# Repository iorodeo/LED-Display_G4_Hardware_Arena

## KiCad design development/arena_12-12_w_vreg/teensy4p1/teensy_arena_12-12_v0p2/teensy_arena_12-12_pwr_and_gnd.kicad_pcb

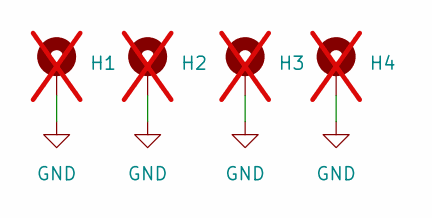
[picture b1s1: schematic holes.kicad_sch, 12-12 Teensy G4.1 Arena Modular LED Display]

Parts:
H1, H2, H3, H4: MountingHole_Pad; MountingHole_4.5mm_Pad; not fitted

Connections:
GND: H1.1, H2.1, H3.1, H4.1; also elsewhere on the board

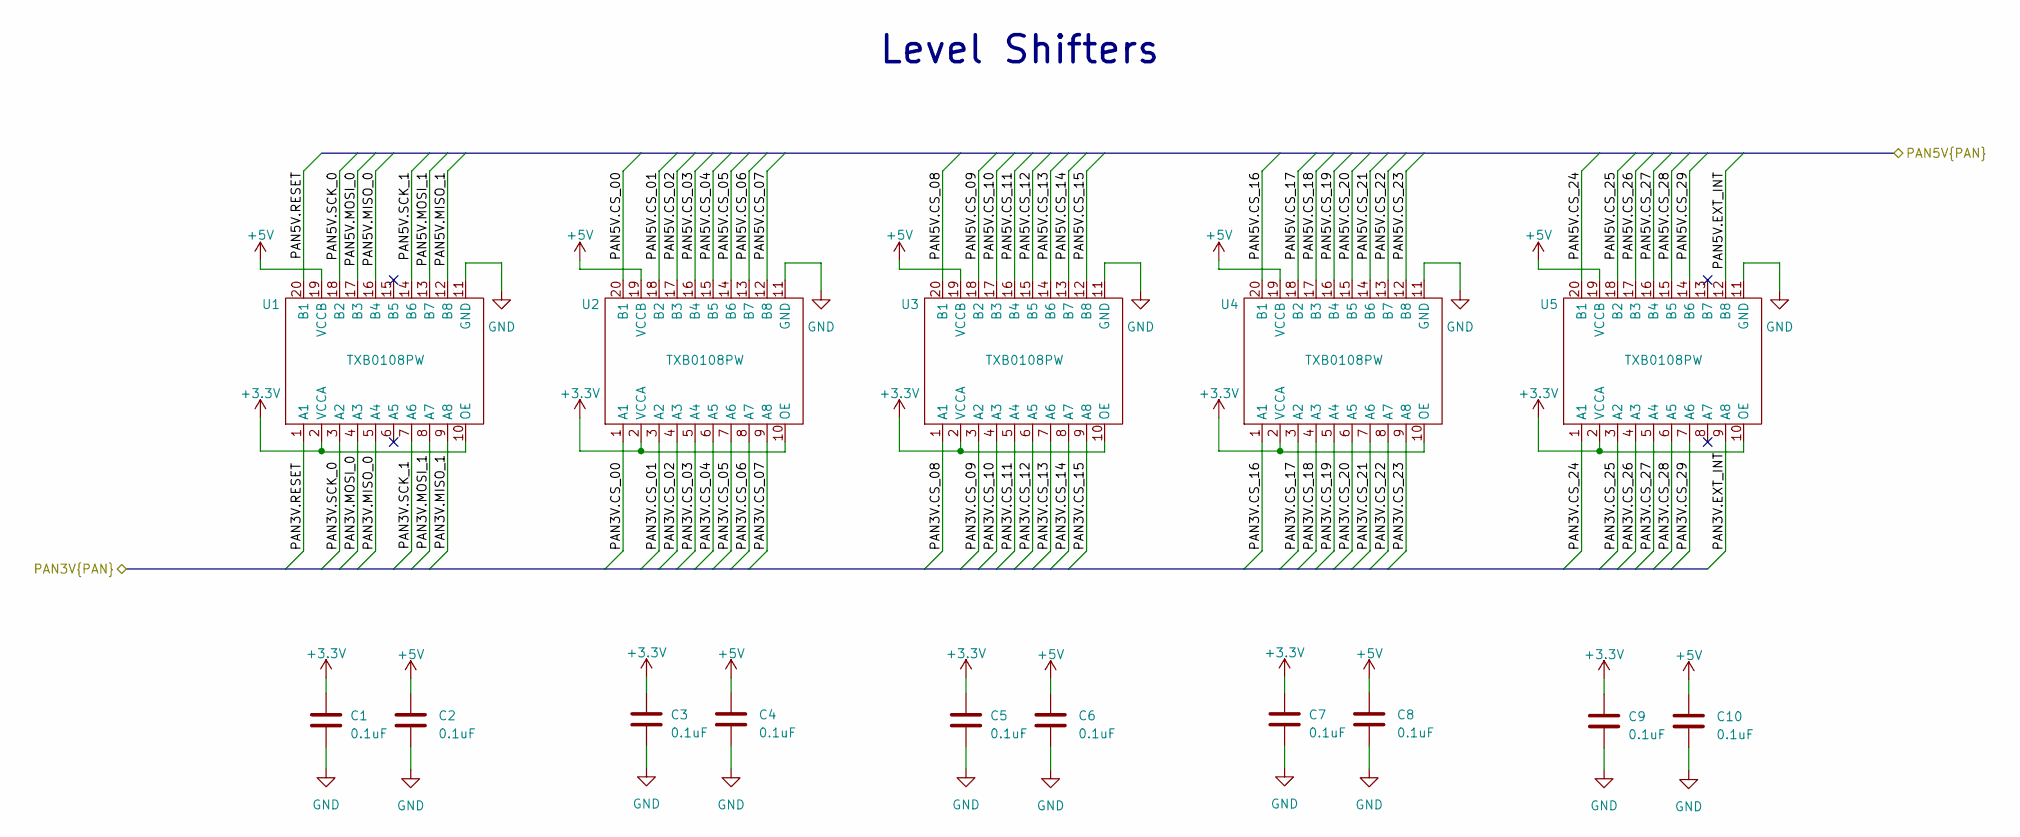
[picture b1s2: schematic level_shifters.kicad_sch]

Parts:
C1, C2, C3, C4, C5, C6, C7, C8, C9, C10: 0.1uF; C_0603_1608Metric
U1, U2, U3, U4, U5: TXB0108PW; TSSOP-20_4.4x6.5mm_P0.65mm

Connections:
+3.3V: C1.1, C3.1, C5.1, C7.1, C9.1, U1.2 (VCCA), U1.10 (OE), U2.2 (VCCA), U2.10 (OE), U3.2 (VCCA), U3.10 (OE), U4.2 (VCCA), U4.10 (OE), U5.2 (VCCA), U5.10 (OE); also elsewhere on the board
+5V: C2.1, C4.1, C6.1, C8.1, C10.1, U1.19 (VCCB), U2.19 (VCCB), U3.19 (VCCB), U4.19 (VCCB), U5.19 (VCCB); also elsewhere on the board
/Level Shifters/PAN3V.CS_00: U2.1 (A1); also elsewhere on the board
/Level Shifters/PAN3V.CS_01: U2.3 (A2); also elsewhere on the board
/Level Shifters/PAN3V.CS_02: U2.4 (A3); also elsewhere on the board
/Level Shifters/PAN3V.CS_03: U2.5 (A4); also elsewhere on the board
/Level Shifters/PAN3V.CS_04: U2.6 (A5); also elsewhere on the board
/Level Shifters/PAN3V.CS_05: U2.7 (A6); also elsewhere on the board
/Level Shifters/PAN3V.CS_06: U2.8 (A7); also elsewhere on the board
/Level Shifters/PAN3V.CS_07: U2.9 (A8); also elsewhere on the board
/Level Shifters/PAN3V.CS_08: U3.1 (A1); also elsewhere on the board
/Level Shifters/PAN3V.CS_09: U3.3 (A2); also elsewhere on the board
/Level Shifters/PAN3V.CS_10: U3.4 (A3); also elsewhere on the board
/Level Shifters/PAN3V.CS_11: U3.5 (A4); also elsewhere on the board
/Level Shifters/PAN3V.CS_12: U3.6 (A5); also elsewhere on the board
/Level Shifters/PAN3V.CS_13: U3.7 (A6); also elsewhere on the board
/Level Shifters/PAN3V.CS_14: U3.8 (A7); also elsewhere on the board
/Level Shifters/PAN3V.CS_15: U3.9 (A8); also elsewhere on the board
/Level Shifters/PAN3V.CS_16: U4.1 (A1); also elsewhere on the board
/Level Shifters/PAN3V.CS_17: U4.3 (A2); also elsewhere on the board
/Level Shifters/PAN3V.CS_18: U4.4 (A3); also elsewhere on the board
/Level Shifters/PAN3V.CS_19: U4.5 (A4); also elsewhere on the board
/Level Shifters/PAN3V.CS_20: U4.6 (A5); also elsewhere on the board
/Level Shifters/PAN3V.CS_21: U4.7 (A6); also elsewhere on the board
/Level Shifters/PAN3V.CS_22: U4.8 (A7); also elsewhere on the board
/Level Shifters/PAN3V.CS_23: U4.9 (A8); also elsewhere on the board
/Level Shifters/PAN3V.CS_24: U5.1 (A1); also elsewhere on the board
/Level Shifters/PAN3V.CS_25: U5.3 (A2); also elsewhere on the board
/Level Shifters/PAN3V.CS_26: U5.4 (A3); also elsewhere on the board
/Level Shifters/PAN3V.CS_27: U5.5 (A4); also elsewhere on the board
/Level Shifters/PAN3V.CS_28: U5.6 (A5); also elsewhere on the board
/Level Shifters/PAN3V.CS_29: U5.7 (A6); also elsewhere on the board
/Level Shifters/PAN3V.EXT_INT: U5.9 (A8); also elsewhere on the board
/Level Shifters/PAN3V.MISO_0: U1.5 (A4); also elsewhere on the board
/Level Shifters/PAN3V.MISO_1: U1.9 (A8); also elsewhere on the board
/Level Shifters/PAN3V.MOSI_0: U1.4 (A3); also elsewhere on the board
/Level Shifters/PAN3V.MOSI_1: U1.8 (A7); also elsewhere on the board
/Level Shifters/PAN3V.RESET: U1.1 (A1); also elsewhere on the board
/Level Shifters/PAN3V.SCK_0: U1.3 (A2); also elsewhere on the board
/Level Shifters/PAN3V.SCK_1: U1.7 (A6); also elsewhere on the board
/Level Shifters/PAN5V.CS_00: U2.20 (B1); also elsewhere on the board
/Level Shifters/PAN5V.CS_01: U2.18 (B2); also elsewhere on the board
/Level Shifters/PAN5V.CS_02: U2.17 (B3); also elsewhere on the board
/Level Shifters/PAN5V.CS_03: U2.16 (B4); also elsewhere on the board
/Level Shifters/PAN5V.CS_04: U2.15 (B5); also elsewhere on the board
/Level Shifters/PAN5V.CS_05: U2.14 (B6); also elsewhere on the board
/Level Shifters/PAN5V.CS_06: U2.13 (B7); also elsewhere on the board
/Level Shifters/PAN5V.CS_07: U2.12 (B8); also elsewhere on the board
/Level Shifters/PAN5V.CS_08: U3.20 (B1); also elsewhere on the board
/Level Shifters/PAN5V.CS_09: U3.18 (B2); also elsewhere on the board
/Level Shifters/PAN5V.CS_10: U3.17 (B3); also elsewhere on the board
/Level Shifters/PAN5V.CS_11: U3.16 (B4); also elsewhere on the board
/Level Shifters/PAN5V.CS_12: U3.15 (B5); also elsewhere on the board
/Level Shifters/PAN5V.CS_13: U3.14 (B6); also elsewhere on the board
/Level Shifters/PAN5V.CS_14: U3.13 (B7); also elsewhere on the board
/Level Shifters/PAN5V.CS_15: U3.12 (B8); also elsewhere on the board
/Level Shifters/PAN5V.CS_16: U4.20 (B1); also elsewhere on the board
/Level Shifters/PAN5V.CS_17: U4.18 (B2); also elsewhere on the board
/Level Shifters/PAN5V.CS_18: U4.17 (B3); also elsewhere on the board
/Level Shifters/PAN5V.CS_19: U4.16 (B4); also elsewhere on the board
/Level Shifters/PAN5V.CS_20: U4.15 (B5); also elsewhere on the board
/Level Shifters/PAN5V.CS_21: U4.14 (B6); also elsewhere on the board
/Level Shifters/PAN5V.CS_22: U4.13 (B7); also elsewhere on the board
/Level Shifters/PAN5V.CS_23: U4.12 (B8); also elsewhere on the board
/Level Shifters/PAN5V.CS_24: U5.20 (B1); also elsewhere on the board
/Level Shifters/PAN5V.CS_25: U5.18 (B2); also elsewhere on the board
/Level Shifters/PAN5V.CS_26: U5.17 (B3); also elsewhere on the board
/Level Shifters/PAN5V.CS_27: U5.16 (B4); also elsewhere on the board
/Level Shifters/PAN5V.CS_28: U5.15 (B5); also elsewhere on the board
/Level Shifters/PAN5V.CS_29: U5.14 (B6); also elsewhere on the board
/Level Shifters/PAN5V.EXT_INT: U5.12 (B8); also elsewhere on the board
/Level Shifters/PAN5V.MISO_0: U1.16 (B4); also elsewhere on the board
/Level Shifters/PAN5V.MISO_1: U1.12 (B8); also elsewhere on the board
/Level Shifters/PAN5V.MOSI_0: U1.17 (B3); also elsewhere on the board
/Level Shifters/PAN5V.MOSI_1: U1.13 (B7); also elsewhere on the board
/Level Shifters/PAN5V.RESET: U1.20 (B1); also elsewhere on the board
/Level Shifters/PAN5V.SCK_0: U1.18 (B2); also elsewhere on the board
/Level Shifters/PAN5V.SCK_1: U1.14 (B6); also elsewhere on the board
GND: C1.2, C2.2, C3.2, C4.2, C5.2, C6.2, C7.2, C8.2, C9.2, C10.2, U1.11 (GND), U2.11 (GND), U3.11 (GND), U4.11 (GND), U5.11 (GND); also elsewhere on the board

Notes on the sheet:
Level Shifters

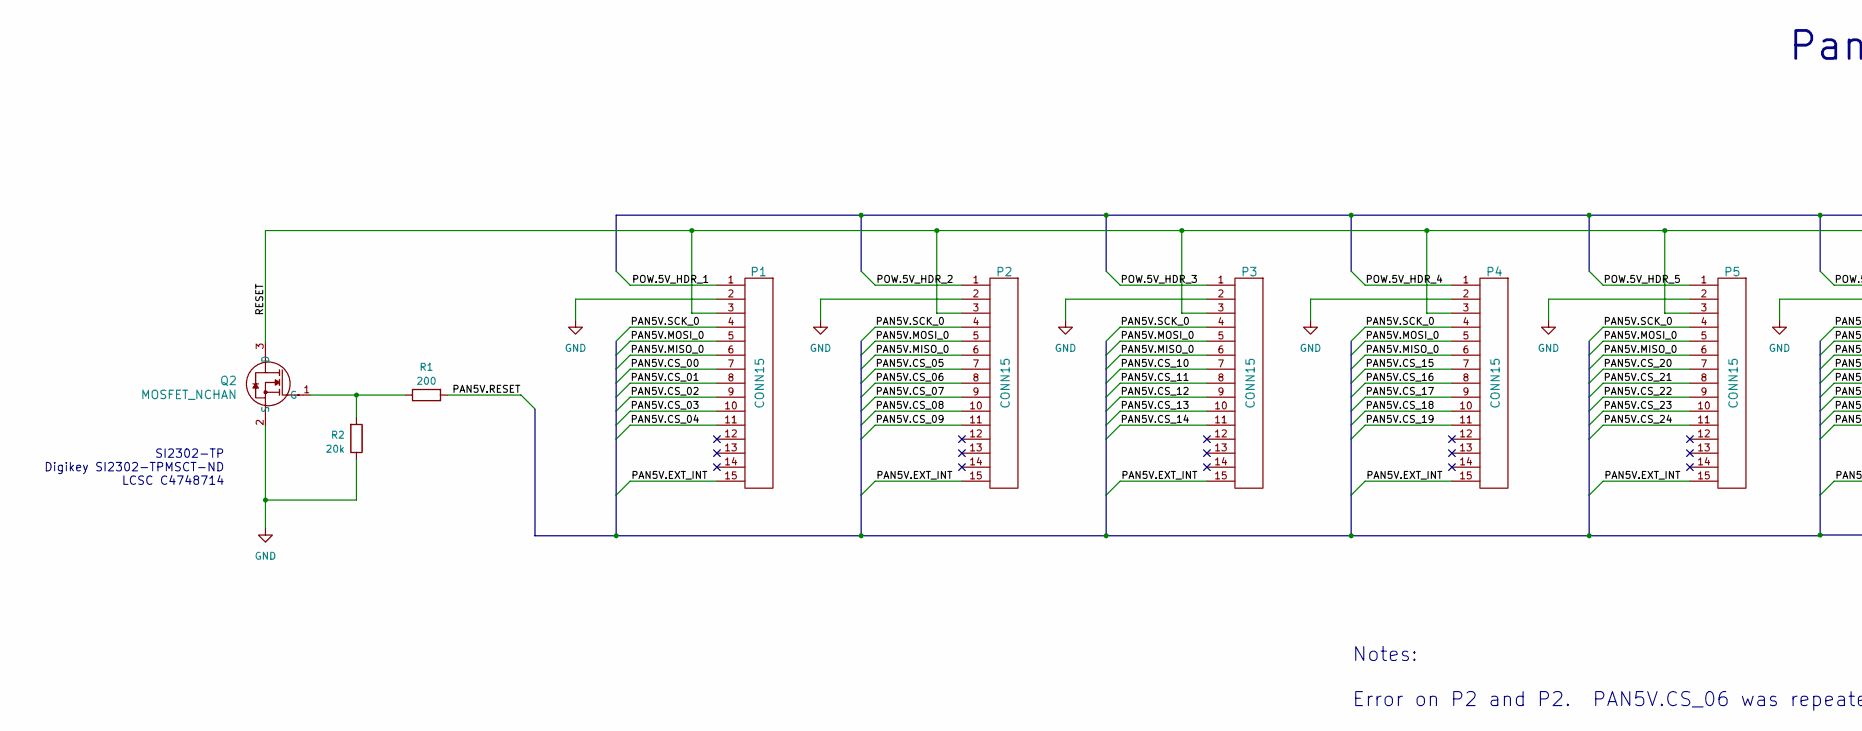
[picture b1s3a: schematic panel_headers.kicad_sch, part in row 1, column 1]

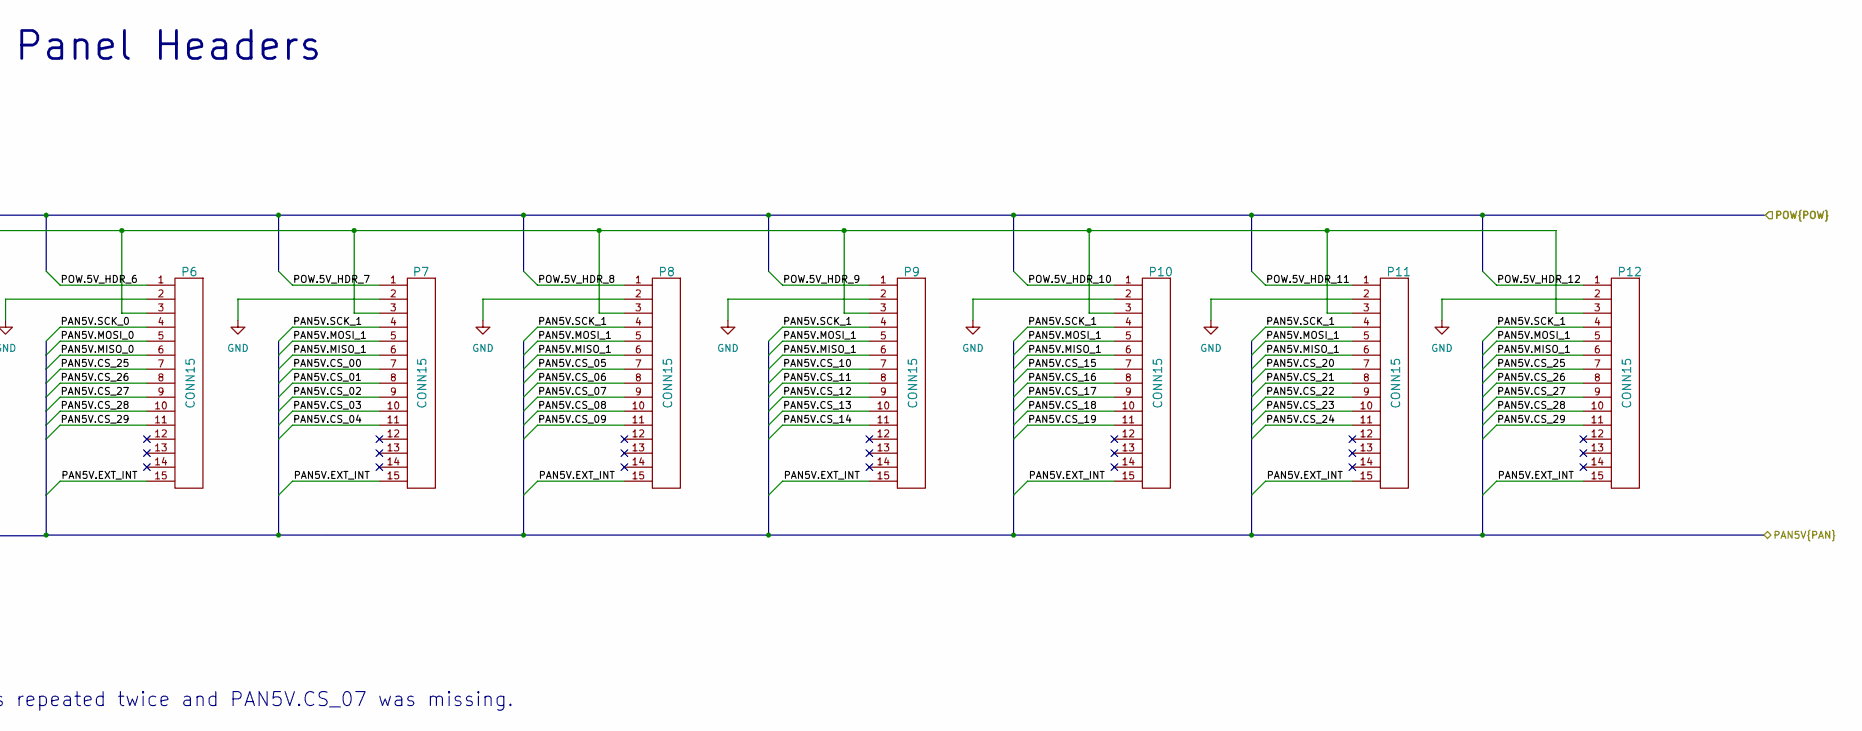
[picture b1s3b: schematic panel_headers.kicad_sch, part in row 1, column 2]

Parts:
P1, P2, P3, P4, P5, P6, P7, P8, P9, P10, P11, P12: CONN15; HEADER_TOP
Q2: MOSFET_NCHAN; SOT-23-3
R1: 200; R_0805_2012Metric
R2: 20k; R_0805_2012Metric

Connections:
/Level Shifters/PAN5V.CS_00: P1.7, P7.7; also elsewhere on the board
/Level Shifters/PAN5V.CS_01: P1.8, P7.8; also elsewhere on the board
/Level Shifters/PAN5V.CS_02: P1.9, P7.9; also elsewhere on the board
/Level Shifters/PAN5V.CS_03: P1.10, P7.10; also elsewhere on the board
/Level Shifters/PAN5V.CS_04: P1.11, P7.11; also elsewhere on the board
/Level Shifters/PAN5V.CS_05: P2.7, P8.7; also elsewhere on the board
/Level Shifters/PAN5V.CS_06: P2.8, P8.8; also elsewhere on the board
/Level Shifters/PAN5V.CS_07: P2.9, P8.9; also elsewhere on the board
/Level Shifters/PAN5V.CS_08: P2.10, P8.10; also elsewhere on the board
/Level Shifters/PAN5V.CS_09: P2.11, P8.11; also elsewhere on the board
/Level Shifters/PAN5V.CS_10: P3.7, P9.7; also elsewhere on the board
/Level Shifters/PAN5V.CS_11: P3.8, P9.8; also elsewhere on the board
/Level Shifters/PAN5V.CS_12: P3.9, P9.9; also elsewhere on the board
/Level Shifters/PAN5V.CS_13: P3.10, P9.10; also elsewhere on the board
/Level Shifters/PAN5V.CS_14: P3.11, P9.11; also elsewhere on the board
/Level Shifters/PAN5V.CS_15: P4.7, P10.7; also elsewhere on the board
/Level Shifters/PAN5V.CS_16: P4.8, P10.8; also elsewhere on the board
/Level Shifters/PAN5V.CS_17: P4.9, P10.9; also elsewhere on the board
/Level Shifters/PAN5V.CS_18: P4.10, P10.10; also elsewhere on the board
/Level Shifters/PAN5V.CS_19: P4.11, P10.11; also elsewhere on the board
/Level Shifters/PAN5V.CS_20: P5.7, P11.7; also elsewhere on the board
/Level Shifters/PAN5V.CS_21: P5.8, P11.8; also elsewhere on the board
/Level Shifters/PAN5V.CS_22: P5.9, P11.9; also elsewhere on the board
/Level Shifters/PAN5V.CS_23: P5.10, P11.10; also elsewhere on the board
/Level Shifters/PAN5V.CS_24: P5.11, P11.11; also elsewhere on the board
/Level Shifters/PAN5V.CS_25: P6.7, P12.7; also elsewhere on the board
/Level Shifters/PAN5V.CS_26: P6.8, P12.8; also elsewhere on the board
/Level Shifters/PAN5V.CS_27: P6.9, P12.9; also elsewhere on the board
/Level Shifters/PAN5V.CS_28: P6.10, P12.10; also elsewhere on the board
/Level Shifters/PAN5V.CS_29: P6.11, P12.11; also elsewhere on the board
/Level Shifters/PAN5V.EXT_INT: P1.15, P2.15, P3.15, P4.15, P5.15, P6.15, P7.15, P8.15, P9.15, P10.15, P11.15, P12.15; also elsewhere on the board
/Level Shifters/PAN5V.MISO_0: P1.6, P2.6, P3.6, P4.6, P5.6, P6.6; also elsewhere on the board
/Level Shifters/PAN5V.MISO_1: P7.6, P8.6, P9.6, P10.6, P11.6, P12.6; also elsewhere on the board
/Level Shifters/PAN5V.MOSI_0: P1.5, P2.5, P3.5, P4.5, P5.5, P6.5; also elsewhere on the board
/Level Shifters/PAN5V.MOSI_1: P7.5, P8.5, P9.5, P10.5, P11.5, P12.5; also elsewhere on the board
/Level Shifters/PAN5V.RESET: R1.2; also elsewhere on the board
/Level Shifters/PAN5V.SCK_0: P1.4, P2.4, P3.4, P4.4, P5.4, P6.4; also elsewhere on the board
/Level Shifters/PAN5V.SCK_1: P7.4, P8.4, P9.4, P10.4, P11.4, P12.4; also elsewhere on the board
/Panel Headers/POW.5V_HDR_1: P1.1; also elsewhere on the board
/Panel Headers/POW.5V_HDR_2: P2.1; also elsewhere on the board
/Panel Headers/POW.5V_HDR_3: P3.1; also elsewhere on the board
/Panel Headers/POW.5V_HDR_4: P4.1; also elsewhere on the board
/Panel Headers/POW.5V_HDR_5: P5.1; also elsewhere on the board
/Panel Headers/POW.5V_HDR_6: P6.1; also elsewhere on the board
/Panel Headers/POW.5V_HDR_7: P7.1; also elsewhere on the board
/Panel Headers/POW.5V_HDR_8: P8.1; also elsewhere on the board
/Panel Headers/POW.5V_HDR_9: P9.1; also elsewhere on the board
/Panel Headers/POW.5V_HDR_10: P10.1; also elsewhere on the board
/Panel Headers/POW.5V_HDR_11: P11.1; also elsewhere on the board
/Panel Headers/POW.5V_HDR_12: P12.1; also elsewhere on the board
/Panel Headers/RESET: P1.3, P2.3, P3.3, P4.3, P5.3, P6.3, P7.3, P8.3, P9.3, P10.3, P11.3, P12.3, Q2.3 (D)
GND: P1.2, P2.2, P3.2, P4.2, P5.2, P6.2, P7.2, P8.2, P9.2, P10.2, P11.2, P12.2, Q2.2 (S), R2.1; also elsewhere on the board
unnamed: Q2.1 (G), R1.1, R2.2

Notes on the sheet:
Notes: Error on P2 and P2. PAN5V.CS_06 was repeated twice and PAN5V.CS_07 was missing.
Panel Headers
SI2302-TP Digikey SI2302-TPMSCT-ND LCSC C4748714

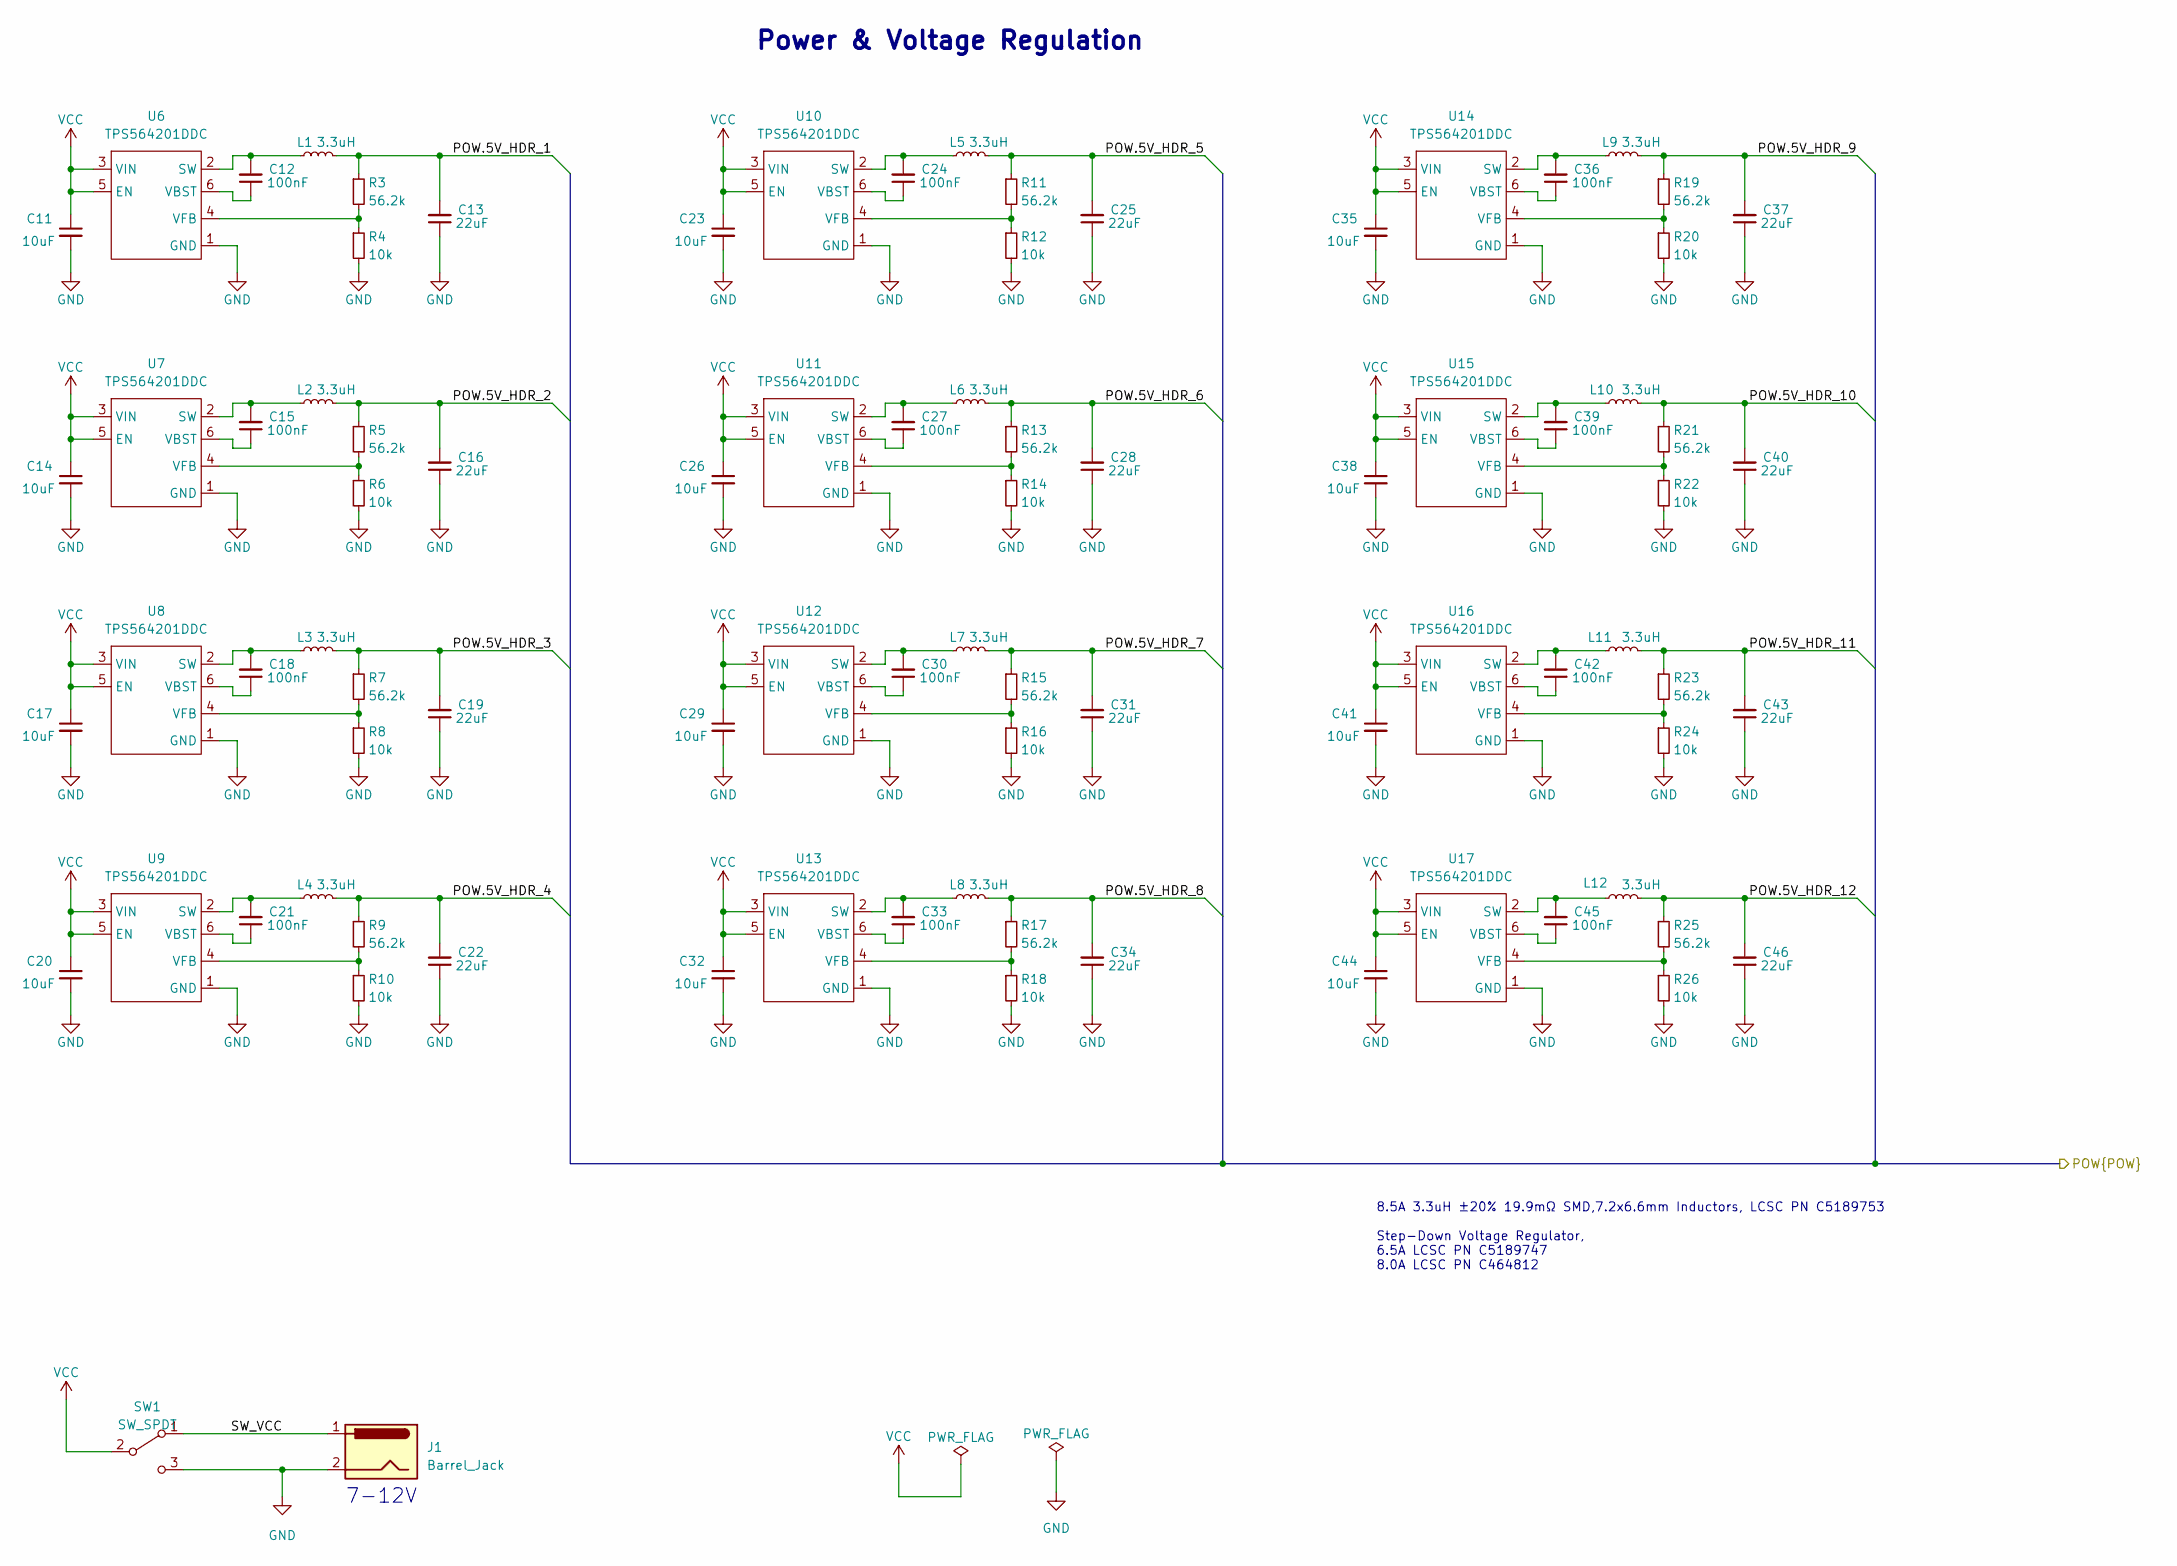
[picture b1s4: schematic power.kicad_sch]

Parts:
C11, C14, C17, C20, C23, C26, C29, C32, C35, C38, C41, C44: 10uF; C_0603_1608Metric
C12, C15, C18, C21, C24, C27, C30, C33, C36, C39, C42, C45: 100nF; C_0603_1608Metric
C13, C16, C19, C22, C25, C28, C31, C34, C37, C40, C43, C46: 22uF; C_0603_1608Metric
J1: Barrel_Jack; DCJACK_2PIN_HIGHCURRENT
L1, L2, L3, L4, L5, L6, L7, L8, L9, L10, L11, L12: 3.3uH; CYA0650_3P3UH
R3, R5, R7, R9, R11, R13, R15, R17, R19, R21, R23, R25: 56.2k; R_0603_1608Metric
R4, R6, R8, R10, R12, R14, R16, R18, R20, R22, R24, R26: 10k; R_0603_1608Metric
SW1: SW_SPDT; slide_switch
U6, U7, U8, U9, U10, U11, U12, U13, U14, U15, U16, U17: TPS564201DDC; SOT-23-6

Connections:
/Panel Headers/POW.5V_HDR_1: C13.2, L1.2, R3.1; also elsewhere on the board
/Panel Headers/POW.5V_HDR_2: C16.2, L2.2, R5.1; also elsewhere on the board
/Panel Headers/POW.5V_HDR_3: C19.2, L3.2, R7.1; also elsewhere on the board
/Panel Headers/POW.5V_HDR_4: C22.2, L4.2, R9.1; also elsewhere on the board
/Panel Headers/POW.5V_HDR_5: C25.2, L5.2, R11.1; also elsewhere on the board
/Panel Headers/POW.5V_HDR_6: C28.2, L6.2, R13.1; also elsewhere on the board
/Panel Headers/POW.5V_HDR_7: C31.2, L7.2, R15.1; also elsewhere on the board
/Panel Headers/POW.5V_HDR_8: C34.2, L8.2, R17.1; also elsewhere on the board
/Panel Headers/POW.5V_HDR_9: C37.2, L9.2, R19.1; also elsewhere on the board
/Panel Headers/POW.5V_HDR_10: C40.2, L10.2, R21.1; also elsewhere on the board
/Panel Headers/POW.5V_HDR_11: C43.2, L11.2, R23.1; also elsewhere on the board
/Panel Headers/POW.5V_HDR_12: C46.2, L12.2, R25.1; also elsewhere on the board
/Power & Voltage Regulators/SW_VCC: J1.1, SW1.1 (A)
GND: C11.2, C13.1, C14.2, C16.1, C17.2, C19.1, C20.2, C22.1, C23.2, C25.1, C26.2, C28.1, C29.2, C31.1, C32.2, C34.1, C35.2, C37.1, C38.2, C40.1, C41.2, C43.1, C44.2, C46.1, J1.2, R4.2, R6.2, R8.2, R10.2, R12.2, R14.2, R16.2, R18.2, R20.2, R22.2, R24.2, R26.2, SW1.3 (C), U6.1 (GND), U7.1 (GND), U8.1 (GND), U9.1 (GND), U10.1 (GND), U11.1 (GND), U12.1 (GND), U13.1 (GND), U14.1 (GND), U15.1 (GND), U16.1 (GND), U17.1 (GND); also elsewhere on the board
unnamed: C12.2, L1.1, U6.2 (SW)
unnamed: C12.1, U6.6 (VBST)
unnamed: R3.2, R4.1, U6.4 (VFB)
unnamed: C15.2, L2.1, U7.2 (SW)
unnamed: C15.1, U7.6 (VBST)
unnamed: R5.2, R6.1, U7.4 (VFB)
unnamed: C18.2, L3.1, U8.2 (SW)
unnamed: C18.1, U8.6 (VBST)
unnamed: R7.2, R8.1, U8.4 (VFB)
unnamed: C21.2, L4.1, U9.2 (SW)
unnamed: C21.1, U9.6 (VBST)
unnamed: R9.2, R10.1, U9.4 (VFB)
unnamed: C24.2, L5.1, U10.2 (SW)
unnamed: C24.1, U10.6 (VBST)
unnamed: R11.2, R12.1, U10.4 (VFB)
unnamed: C27.2, L6.1, U11.2 (SW)
unnamed: C27.1, U11.6 (VBST)
unnamed: R13.2, R14.1, U11.4 (VFB)
unnamed: C30.2, L7.1, U12.2 (SW)
unnamed: C30.1, U12.6 (VBST)
unnamed: R15.2, R16.1, U12.4 (VFB)
unnamed: C33.2, L8.1, U13.2 (SW)
unnamed: C33.1, U13.6 (VBST)
unnamed: R17.2, R18.1, U13.4 (VFB)
unnamed: C36.2, L9.1, U14.2 (SW)
unnamed: C36.1, U14.6 (VBST)
unnamed: R19.2, R20.1, U14.4 (VFB)
unnamed: C39.2, L10.1, U15.2 (SW)
unnamed: C39.1, U15.6 (VBST)
unnamed: R21.2, R22.1, U15.4 (VFB)
unnamed: C42.2, L11.1, U16.2 (SW)
unnamed: C42.1, U16.6 (VBST)
unnamed: R23.2, R24.1, U16.4 (VFB)
unnamed: C45.2, L12.1, U17.2 (SW)
unnamed: C45.1, U17.6 (VBST)
unnamed: R25.2, R26.1, U17.4 (VFB)
VCC: C11.1, C14.1, C17.1, C20.1, C23.1, C26.1, C29.1, C32.1, C35.1, C38.1, C41.1, C44.1, SW1.2 (B), U6.3 (VIN), U6.5 (EN), U7.3 (VIN), U7.5 (EN), U8.3 (VIN), U8.5 (EN), U9.3 (VIN), U9.5 (EN), U10.3 (VIN), U10.5 (EN), U11.3 (VIN), U11.5 (EN), U12.3 (VIN), U12.5 (EN), U13.3 (VIN), U13.5 (EN), U14.3 (VIN), U14.5 (EN), U15.3 (VIN), U15.5 (EN), U16.3 (VIN), U16.5 (EN), U17.3 (VIN), U17.5 (EN)

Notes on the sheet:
7-12V
8.5A 3.3uH ±20% 19.9mΩ SMD,7.2x6.6mm Inductors, LCSC PN C5189753 Step-Down Voltage Regulator, 6.5A LCSC PN C5189747 8.0A LCSC PN C464812
Power & Voltage Regulation

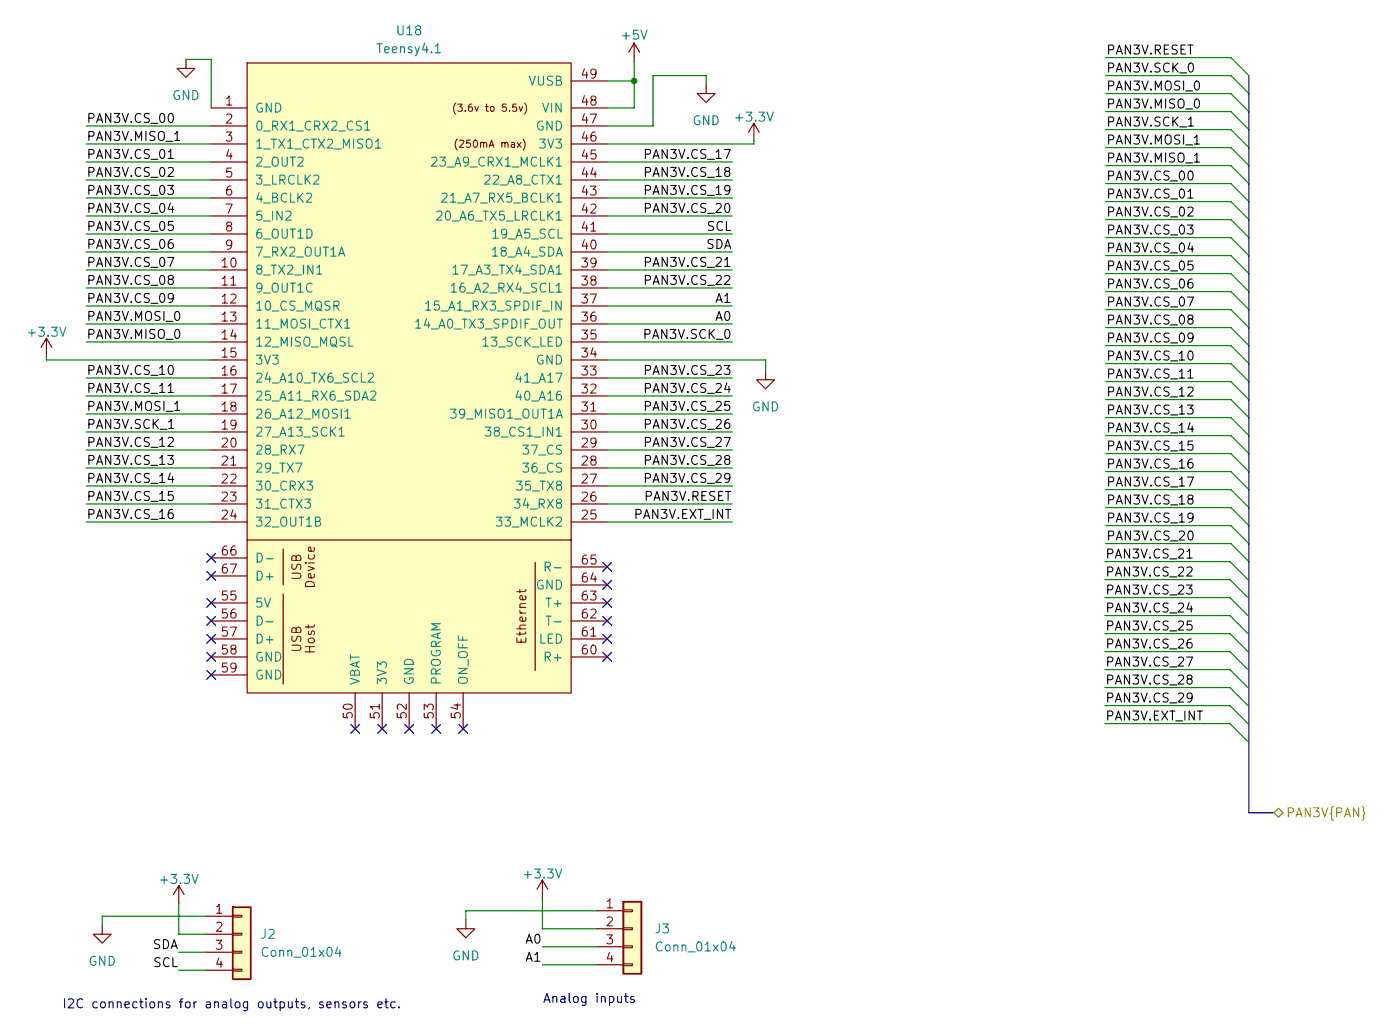
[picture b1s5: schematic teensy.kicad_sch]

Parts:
J2, J3: Conn_01x04; JST_SH_SM04B-SRSS-TB_1x04-1MP_P1.00mm_Horizontal
U18: Teensy4.1; Teensy41

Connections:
+3.3V: J2.2, J3.2, U18.15 (3V3), U18.46 (3V3); also elsewhere on the board
+5V: U18.48 (VIN), U18.49 (VUSB); also elsewhere on the board
/Level Shifters/PAN3V.CS_00: U18.2 (0_RX1_CRX2_CS1); also elsewhere on the board
/Level Shifters/PAN3V.CS_01: U18.4 (2_OUT2); also elsewhere on the board
/Level Shifters/PAN3V.CS_02: U18.5 (3_LRCLK2); also elsewhere on the board
/Level Shifters/PAN3V.CS_03: U18.6 (4_BCLK2); also elsewhere on the board
/Level Shifters/PAN3V.CS_04: U18.7 (5_IN2); also elsewhere on the board
/Level Shifters/PAN3V.CS_05: U18.8 (6_OUT1D); also elsewhere on the board
/Level Shifters/PAN3V.CS_06: U18.9 (7_RX2_OUT1A); also elsewhere on the board
/Level Shifters/PAN3V.CS_07: U18.10 (8_TX2_IN1); also elsewhere on the board
/Level Shifters/PAN3V.CS_08: U18.11 (9_OUT1C); also elsewhere on the board
/Level Shifters/PAN3V.CS_09: U18.12 (10_CS_MQSR); also elsewhere on the board
/Level Shifters/PAN3V.CS_10: U18.16 (24_A10_TX6_SCL2); also elsewhere on the board
/Level Shifters/PAN3V.CS_11: U18.17 (25_A11_RX6_SDA2); also elsewhere on the board
/Level Shifters/PAN3V.CS_12: U18.20 (28_RX7); also elsewhere on the board
/Level Shifters/PAN3V.CS_13: U18.21 (29_TX7); also elsewhere on the board
/Level Shifters/PAN3V.CS_14: U18.22 (30_CRX3); also elsewhere on the board
/Level Shifters/PAN3V.CS_15: U18.23 (31_CTX3); also elsewhere on the board
/Level Shifters/PAN3V.CS_16: U18.24 (32_OUT1B); also elsewhere on the board
/Level Shifters/PAN3V.CS_17: U18.45 (23_A9_CRX1_MCLK1); also elsewhere on the board
/Level Shifters/PAN3V.CS_18: U18.44 (22_A8_CTX1); also elsewhere on the board
/Level Shifters/PAN3V.CS_19: U18.43 (21_A7_RX5_BCLK1); also elsewhere on the board
/Level Shifters/PAN3V.CS_20: U18.42 (20_A6_TX5_LRCLK1); also elsewhere on the board
/Level Shifters/PAN3V.CS_21: U18.39 (17_A3_TX4_SDA1); also elsewhere on the board
/Level Shifters/PAN3V.CS_22: U18.38 (16_A2_RX4_SCL1); also elsewhere on the board
/Level Shifters/PAN3V.CS_23: U18.33 (41_A17); also elsewhere on the board
/Level Shifters/PAN3V.CS_24: U18.32 (40_A16); also elsewhere on the board
/Level Shifters/PAN3V.CS_25: U18.31 (39_MISO1_OUT1A); also elsewhere on the board
/Level Shifters/PAN3V.CS_26: U18.30 (38_CS1_IN1); also elsewhere on the board
/Level Shifters/PAN3V.CS_27: U18.29 (37_CS); also elsewhere on the board
/Level Shifters/PAN3V.CS_28: U18.28 (36_CS); also elsewhere on the board
/Level Shifters/PAN3V.CS_29: U18.27 (35_TX8); also elsewhere on the board
/Level Shifters/PAN3V.EXT_INT: U18.25 (33_MCLK2); also elsewhere on the board
/Level Shifters/PAN3V.MISO_0: U18.14 (12_MISO_MQSL); also elsewhere on the board
/Level Shifters/PAN3V.MISO_1: U18.3 (1_TX1_CTX2_MISO1); also elsewhere on the board
/Level Shifters/PAN3V.MOSI_0: U18.13 (11_MOSI_CTX1); also elsewhere on the board
/Level Shifters/PAN3V.MOSI_1: U18.18 (26_A12_MOSI1); also elsewhere on the board
/Level Shifters/PAN3V.RESET: U18.26 (34_RX8); also elsewhere on the board
/Level Shifters/PAN3V.SCK_0: U18.35 (13_SCK_LED); also elsewhere on the board
/Level Shifters/PAN3V.SCK_1: U18.19 (27_A13_SCK1); also elsewhere on the board
/Teensy/A0: J3.3, U18.36 (14_A0_TX3_SPDIF_OUT)
/Teensy/A1: J3.4, U18.37 (15_A1_RX3_SPDIF_IN)
/Teensy/SCL: J2.4, U18.41 (19_A5_SCL)
/Teensy/SDA: J2.3, U18.40 (18_A4_SDA)
GND: J2.1, J3.1, U18.1 (GND), U18.34 (GND), U18.47 (GND); also elsewhere on the board

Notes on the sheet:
Analog inputs
I2C connections for analog outputs, sensors etc.

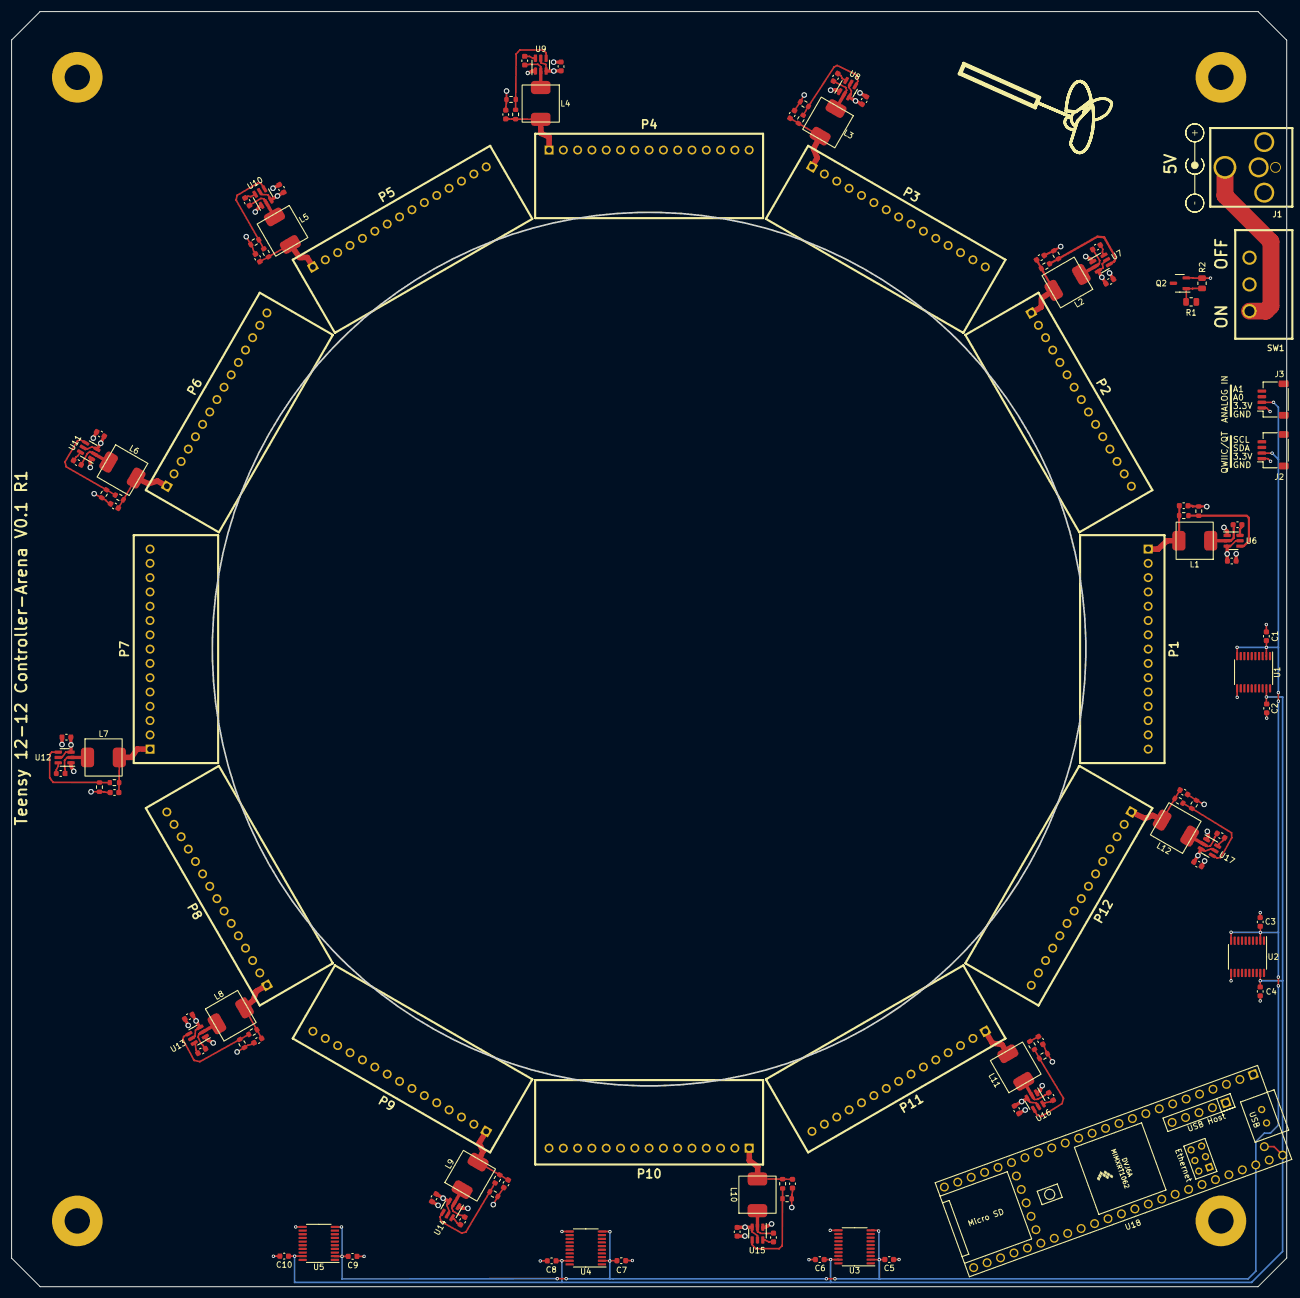
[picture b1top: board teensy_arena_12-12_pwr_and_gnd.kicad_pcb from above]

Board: 4 copper layers, 226.6 x 226.6 mm, 123 parts (0 on the bottom side), 135 nets.

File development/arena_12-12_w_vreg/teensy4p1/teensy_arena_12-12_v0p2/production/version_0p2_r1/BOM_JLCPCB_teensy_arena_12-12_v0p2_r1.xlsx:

Comment | Designator | Footprint | LCSC Part #（optional） | Qty
0.1uF ceramic Capacitor | C1, C2, C3, C4, C5, C6, C7, C8, C9, C10 | 0603 | C1591 | 10
10uF Ceramic Capacitor, 25V | C11, C14, C17, C20, C23, C26, C29, C32, C35, C38, C41, C44 | 0603 | C96446 | 12
100nF Ceramic Capacitor | C12, C15, C18, C21, C24, C27, C30, C33, C36, C39, C42, C45 | 0603 | C1591 | 12
22uF Ceramic Capacitor | C13, C16, C19, C22, C25, C28, C31, C34, C37, C40, C43, C46 | 0603 | C2762594 | 12
3.3uH Inductor | L1, L2, L3, L4, L5, L6, L7, L8, L9, L10, L11, L12 | SMD,7.2x6.6mm | C5189747 | 12
200 Ohm resistor | R1 | 0805 | C17540 | 1
20k Ohms resistor | R2 | 0805 | C4328 | 1
56.2k Resistor, 0.1% | R3, R5, R7, R9, R11, R13, R15, R17, R19, R21, R23, R25 | 0603 | C705784 | 12
10k Resistor, 0.1% | R4, R6, R8, R10, R12, R14, R16, R18, R20, R22, R24, R26 | 0603 | C95204 | 12
MOSFET N-channel | Q2 | SOT-23 | C165220 | 1
Level shifter TXB0108PWR | U1,U2,U3,U4,U5 | TSSOP-20 | C53406 | 5
TPS564201DDC Step-Down Regulator | U6, U7, U8, U9, U10, U11, U12, U13, U14, U15, U16, U17 | TSOT-23-6 | C464812 | 12
4-Pin Connector, JST SM04B-SRSS-TB or similar | J2 ,J3 | SMD,P=1mm | C145956 | 2
DC Power Barrel Jack | J1 | through hole | global parts | 1
15x1 female header, 0.1in pitch | P1,P2,P3,P4,P5,P6,P7,P8,P9,P10,P11,P12 | through hole | global parts | 12
Slide Switch SPDT | SW1 | through hole | global parts | 1
Teensy4.1 | U18 | through hole | global parts | 1
